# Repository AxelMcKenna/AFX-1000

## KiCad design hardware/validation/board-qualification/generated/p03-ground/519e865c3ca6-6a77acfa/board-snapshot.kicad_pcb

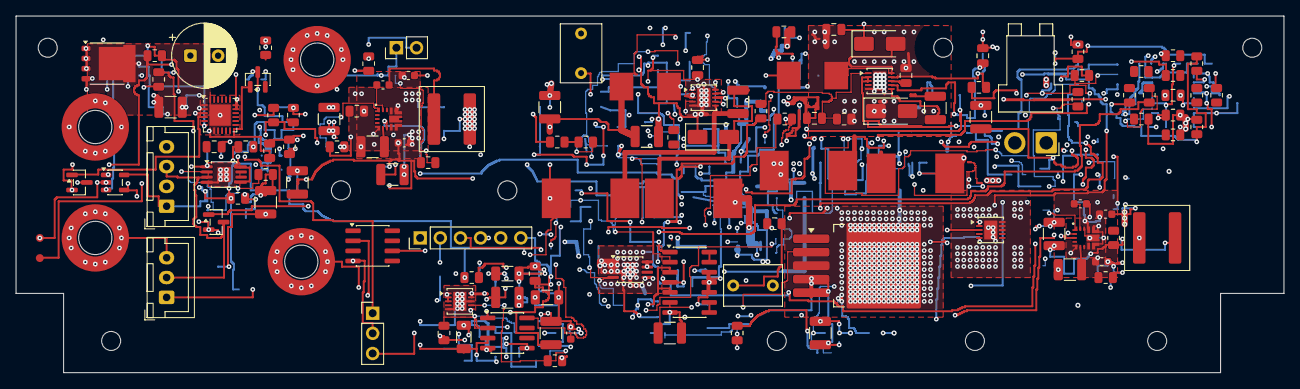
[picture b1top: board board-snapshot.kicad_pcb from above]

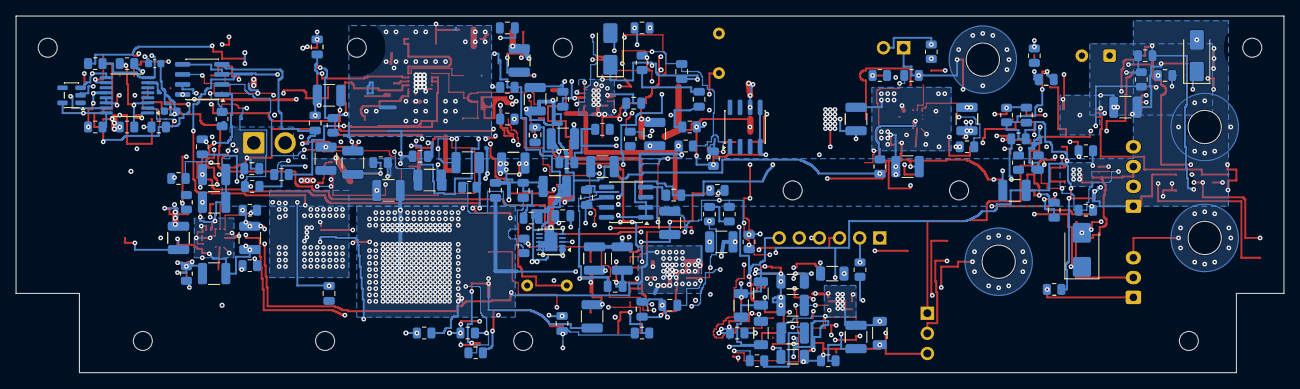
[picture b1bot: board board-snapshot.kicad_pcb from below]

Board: 6 copper layers, 160.0 x 45.0 mm, 261 parts (129 on the bottom side), 108 nets.

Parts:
C1, C63: 10uF 63V X7R; C_1210_3225Metric
C2, C3, C5, C6, C8, C9, C37, C42, C52, C57, C64, C65, C67, C68, C70: 22uF 50V X7R; C_1210_3225Metric
C4, C7, C10, C35, C38, C40, C43, C50, C53, C55, C58, C59, C61, C66, C69, C71: 100nF 50V X7R; C_0805_2012Metric
C11, C30, C72, C107, C108: 100nF 16V X7R; C_0805_2012Metric
C12, C14, C73, C75: 68pF 50V C0G 5%; C_0805_2012Metric
C13, C15, C74, C76: 330nF 16V X7R; C_0805_2012Metric
C31: 2.2uF 16V X7R; C_0805_2012Metric
C32, C33: 1uF film 63V 10% MKS2C041001F00KSSD; C_Rect_L7.2mm_W5.0mm_P5.00mm
C34, C39, C49, C54, C240: 47nF 50V C0G 5%; C_1210_3225Metric
C36, C41, C51, C56: 10uF 50V X7R; C_1210_3225Metric
C60, C62, C105: 1uF 50V X7R; C_0805_2012Metric
C101, C102: 2.2uF 100V X7R; C_1210_3225Metric
C103: 220uF 35V electrolytic 20% (EEUFR1V221); CP_Radial_D8.0mm_P3.50mm
C104: 1uF 50V X7R; C_1210_3225Metric
C106: 10uF 16V X7R; C_1210_3225Metric
C109: 1nF 16V C0G 5%; C_0805_2012Metric
C110: 10nF 16V C0G 5%; C_0805_2012Metric
C200, C220: 4.7uF 16V X7R; C_1210_3225Metric
C201, C202, C203, C221, C222, C223, C255, C301, C302: 100nF 50V X7R; C_0603_1608Metric
C204, C205, C224, C225: 22uF 25V X7R; C_1210_3225Metric
C206, C207, C208, C209, C226, C227, C228, C229: 47uF 16V X7R; C_1210_3225Metric
C241: 1uF 25V X7R; C_1210_3225Metric
C242, C243, C244, C245, C246, C247, C248, C249, C250, C251: 100nF 25V C0G 5% KEMET C1206C104J3GACTU; C_1206_3216Metric
C252, C253: 1uF 16V X7R; C_1210_3225Metric
C254: 22uF 16V X7R; C_1210_3225Metric
C300: 10nF 50V C0G 5%; C_0805_2012Metric
D1, D2, D3, D4, D103: SS16-E3/61T; D_SMA
D101: SMBJ33CA-E3/52; D_SMB
D102: BAS116,215; SOT-23
H1, H2, H3, H4, H5, H6, H7, H8, H9, H10: M2_CLEARANCE; M2_Clearance
J2: Header6; PinHeader_1x06_P2.54mm_Vertical
J3: Header2; PinHeader_1x02_P2.54mm_Vertical
J20, J21, J23, J24: Wurth 7466003R M3 SMT; Wurth_7466003R
J22: P03 READY test; PinHeader_1x03_P2.54mm_Vertical
J101: JST B2PS-VH (VHR-2N/SVH-41T-P1.1 AWG16); JST_VH_B2PS-VH_1x02_P3.96mm_Horizontal
J103: Bare POWER_READY probe pads, no fitted header; Probe2_P2.54_D1
J104: JST B3B-XH-A (XHP-3/SXH-001T-P0.6); JST_XH_B3B-XH-A_1x03_P2.50mm_Vertical
J106: JST B4B-XH-A (XHP-4/SXH-001T-P0.6); JST_XH_B4B-XH-A_1x04_P2.50mm_Vertical
L1, L6: 33uH 20% SRP7050WA-330M; SRP7050WA
L2, L3, L7, L8: 68uH 20% SRP1050WA-680M; SRP1050WA
L20, L23: 4.7uH 20% Coilcraft XAL7030-472MEC; L_Coilcraft_XAL7030-472
Q101: PSMN012-100YL,115; LFPAK56
Q102: BSS138-7-F; SOT-23
Q103: DMN2056U-7; SOT-23
R1: 300k 0.01% 5ppm; R_0805_2012Metric
R2, R3, R4, R45, R46: 15k 0.01% 5ppm; R_0805_2012Metric
R5, R20, R21, R34, R35: 330k 0.01% 5ppm; R_0805_2012Metric
R6, R7, R49, R50, R316: 4.7k 1%; R_0805_2012Metric
R17, R19, R110: 1k 1%; R_0805_2012Metric
R18, R120: 100k 1%; R_0805_2012Metric
R22, R27, R36, R41, R243, R244: 100k 0.01% 5ppm; R_0805_2012Metric
R23, R28, R37, R42, R241: 6.8k 1%; R_0805_2012Metric
R24, R38: 9.09k 1%; R_0805_2012Metric
R25, R39, R47, R306: 200k 0.01% 5ppm; R_0805_2012Metric
R26, R40, R308: 180k 0.01% 5ppm; R_0805_2012Metric
R29, R43: 5.62k 1%; R_0805_2012Metric
R44: 240k 0.01% 5ppm; R_0805_2012Metric
R48, R301, R303, R305, R307, R309, R314: 10k 0.01% 5ppm; R_0805_2012Metric
R101, R103, R117: 309k 0.1% 10ppm; R_0805_2012Metric
R102: 40.2k 0.1% 10ppm; R_0805_2012Metric
R104: 28k 0.1% 10ppm; R_0805_2012Metric
R105: 68.1k 0.1% 10ppm; R_0805_2012Metric
R106, R109, R118, R119: 10k 0.1% 10ppm; R_0805_2012Metric
R107: 4.02k 0.1% 10ppm; R_0805_2012Metric
R108: 11.4k 0.1% 10ppm; R_0805_2012Metric
R111, R204, R224, R246: 10k 1%; R_0805_2012Metric
R112, R114: 47k 1%; R_0805_2012Metric
R113: 3.3k 1%; R_0805_2012Metric
R115: 30.9k 0.1% 10ppm; R_0805_2012Metric
R116: 3.09k 0.1% 10ppm; R_0805_2012Metric
R121: 100 1%; R_0805_2012Metric
R130: 49.9 0.01% 5ppm; R_0805_2012Metric
R200: 9k 0.01% 2ppm Susumu RG2012L-902-L-T1; R_0805_2012Metric
R201: 1k 0.01% 2ppm Susumu RG2012L-102-L-T1; R_0805_2012Metric
R202, R222: 24.3k 1%; R_0805_2012Metric
R203, R223: 3.32k 1%; R_0805_2012Metric
R205, R225: 22k 1%; R_0805_2012Metric
R206: 54.9 0.1% 25ppm Panasonic ERA6AEB549V; R_0805_2012Metric
R220: 11k 0.01% 5ppm; R_0805_2012Metric
R221, R311: 1k 0.01% 5ppm; R_0805_2012Metric
R240: 100 0.01% 5ppm; R_0805_2012Metric
R242: 120 0.01% 5ppm; R_0805_2012Metric
R245: 2.21k 1%; R_0805_2012Metric
R300, R302: 87.6k 0.01% 5ppm; R_0805_2012Metric
R304: 324k 0.01% 5ppm; R_0805_2012Metric
R310: 590 0.01% 5ppm; R_0805_2012Metric
R312: 7.5k 0.01% 5ppm; R_0805_2012Metric
R313: 1M 0.01% 5ppm; R_0805_2012Metric
R315: 750k 0.01% 5ppm; R_0805_2012Metric
U1, U13: LT3471EDD#PBF; DFN-10-1EP_3x3mm_P0.5mm_EP1.65x2.38mm
U4: REF5025EIDR; SOIC-8_3.9x4.9mm_P1.27mm
U5: OPA4192ID; SOIC-14_3.9x8.7mm_P1.27mm
U6, U24: OPA2192ID; SOIC-8_3.9x4.9mm_P1.27mm
U7: LT3080IMS8E#PBF; MSOP-8-1EP_3x3mm_P0.65mm_EP1.68x1.88mm
U8: LT3080IQ#PBF; TO-263-5_TabPin3
U10, U11: LT3090IDD#PBF; DFN-10-1EP_3x3mm_P0.5mm_EP1.65x2.38mm
U12: LT1634AIS8-2.5#PBF; SOIC-8_3.9x4.9mm_P1.27mm
U20, U23: TPS543620RPYR; TPS543620_RPY0014A
U21: ADR4550BRZ; SOIC-8_3.9x4.9mm_P1.27mm
U22: LT3045IDD#PBF; DFN-10-1EP_3x3mm_P0.5mm_EP1.65x2.38mm
U25: LTC2910HGN#PBF; SSOP-16_3.9x4.9mm_P0.635mm
U26: SN74LVC1G08DBVR; SOT-23-5
U101: TPS26630RGER; Texas_RGE0024H_VQFN-24-1EP_4x4mm_P0.5mm_EP2.7x2.7mm
U102: TPS7A1601DGNR; MSOP-8-1EP_3x3mm_P0.65mm_EP1.68x1.88mm
U103: TLV7011DBVR; SOT-23-5

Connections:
/5V_DIG_SRC: C30.1, C206.1, C207.1, C208.1, C209.1, J3.1, J23.1, L20.2, R6.1, R7.1, R49.1, R50.1, R200.1, R300.1, U4.1, U4.2, U10.5, U11.5
/AGND: C2.2, C3.2, C4.2, C5.2, C6.2, C7.2, C8.2, C9.2, C10.2, C11.2, C13.2, C15.2, C30.2, C31.2, C32.2, C33.2, C35.2, C36.2, C37.2, C38.2, C40.2, C41.2, C42.2, C43.2, C50.2, C51.2, C52.2, C53.2, C55.2, C56.2, C57.2, C58.2, C59.2, C60.2, C61.2, C62.2, C64.2, C65.2, C66.2, C67.2, C68.2, C69.2, C70.2, C71.2, C72.2, C74.2, C76.2, C101.2, C102.2, C103.2, C104.2, C105.2, C106.2, C107.2, C108.2, C109.2, C110.2, C200.2, C202.2, C203.2, C204.2, C205.2, C206.2, C207.2, C208.2, C209.2, C220.2, C222.2, C223.2, C224.2, C225.2, C226.2, C227.2, C228.2, C229.2, C241.2, C242.2, C243.2, C244.2, C245.2, C246.2, C247.2, C248.2, C249.2, C250.2, C251.2, C252.2, C253.2, C254.2, C255.2, C300.2, C301.2, C302.2, D2.1, D4.1, D101.2, D103.2, J2.2, J3.2, J20.1, J21.1, J22.2, J101.2, J103.1, J104.3, J106.2, Q103.2, R3.2, R22.2, R24.2, R27.2, R29.2, R36.2, R38.2, R41.2, R43.2, R45.2, R102.2, R104.2, R106.2, R107.2, R109.2, R111.2, R112.2, R114.2, R116.2, R119.2, R120.2, R201.2, R202.2, R203.2, R205.2, R221.2, R222.2, R223.2, R225.2, R243.2, R245.2, R301.2, R303.2, R305.2, R307.2, R309.2, R311.2, U1.5, U1.11, U4.4, U5.10, U5.11, U5.12, U6.8, U10.3, U11.3, U12.6, U13.5, U13.11, U20.5, U20.9, U20.11, U21.4, U22.5, U22.8, U22.11, U23.5, U23.9, U23.11, U24.4, U24.5, U25.9, U25.13, U25.14, U26.3, U101.8, U101.25, U102.4, U102.9, U103.2
/AUX_FB: R109.1, R130.2, U102.2
/AUX_START_DELAY: C110.1, U102.7
/BLOCK_DRV: Q102.1, U101.4
/BLOCK_GATE: Q101.4, Q102.3, U101.3
/CUK_NODE: C1.2, D2.2, L3.1
/DC_IN: C101.1, D101.1, J101.1, Q101.1, Q101.2, Q101.3, Q102.2, R101.1, R103.1, U101.5
/FAST_OV_GATE: Q103.1, R120.1, R121.2
/FAST_OV_OUT: R117.1, R121.1, U103.1
/FAST_OV_REF: C109.1, R118.2, R119.1, U103.4
/FAST_OV_SENSE: R115.2, R116.1, R117.2, U103.3
/INPUT_ILIM: R107.1, U101.10
/INPUT_OV: D102.1, R103.2, R104.1, U101.7
/INPUT_PGTH: R105.2, R106.1, U101.15
/INPUT_SLEW: C105.1, U101.9
/INPUT_UV: R101.2, R102.1, U101.6
/LO_CUK_NODE: C63.2, D4.2, L8.1
/LO_N_FB: C75.2, R46.2, R47.1, U13.4
/LO_N_RMID: R47.2, R48.1
/LO_N_SS: C76.1, R50.2, U13.7
/LO_N_SW: C63.1, L7.2, U13.6
/LO_P_FB: C73.2, R44.2, R45.1, U13.1
/LO_P_SS: C74.1, R49.2, U13.9
/LO_P_SW: D3.2, L6.2, U13.10
/LO_REF_1V: C72.1, R46.1, U13.2, U13.3
/N12_DRIVE: C54.1, R42.1, U6.7
/N12_FB: C54.2, R40.2, R41.1, U6.6
/N12_RMID: R39.2, R40.1
/N12_SET: C55.1, R39.1, R42.2, U11.4
/N12_SRC: C57.1, C58.1, J2.5, R43.1, R315.2, U11.1, U11.2
/N19_DRIVE: C49.1, R37.1, U6.1
/N19_FB: C49.2, R35.2, R36.1, U6.2
/N19_RMID: R34.2, R35.1
/N19_SET: C50.1, R34.1, R37.2, U10.4
/N19_SRC: C52.1, C53.1, J2.3, R38.1, R313.2, U10.1, U10.2
/NREF_2V5: R18.1, R19.1, U12.4, U12.5
/NREF_FILTER: C33.1, R19.2, U6.3, U6.5
/P03_ALL_SOURCES_READY: J22.1, J106.4, R316.2, U25.12
/P03_ANA_DIV: R242.2, R243.1, R244.1
/P03_ANA_DRIVE: C240.1, R241.1, U24.1
/P03_ANA_FB: C240.2, R244.2, U24.2
/P03_ANA_SET: C241.1, R241.2, R242.1, U22.7
/P03_AUX_TRIM: R108.2, R130.1
/P03_A_BOOT: C221.1, U23.14
/P03_A_BP5: C220.1, U23.6
/P03_A_ENABLE: R224.2, R225.1, U23.7
/P03_A_FB: R220.2, R221.1, U23.4
/P03_A_FSEL: R222.1, U23.1
/P03_A_MODE: R223.1, U23.2
/P03_A_SW: C221.2, L23.1, U23.10, U23.13
/P03_D_BOOT: C201.1, U20.14
/P03_D_BP5: C200.1, U20.6
/P03_D_ENABLE: R204.2, R205.1, U20.7
/P03_D_FB: R201.1, R206.2, U20.4
/P03_D_FB_TRIM: R200.2, R206.1
/P03_D_FSEL: R202.1, U20.1
/P03_D_MODE: R203.1, U20.2
/P03_D_SW: C201.2, L20.1, U20.10, U20.13
/P03_MON_ANA: R302.2, R303.1, U25.2
/P03_MON_BUCK_OK: U25.5, U26.4
/P03_MON_DIG: R300.2, R301.1, U25.1
/P03_MON_N12: R314.2, R315.1, U25.8
/P03_MON_N19: R312.2, R313.1, U25.7
/P03_MON_NEG_BIAS: R310.2, R311.1, R312.1, R314.1
/P03_MON_P12: R306.2, R307.1, U25.4
/P03_MON_P19: R304.2, R305.1, U25.3
/P03_MON_REF: R310.1, U25.10
/P03_MON_TIMER: C300.1, U25.15
/P03_MON_VIN: R308.2, R309.1, U25.6
/P03_PRE6V: C226.1, C227.1, C228.1, C229.1, C253.1, L23.2, R220.1, U21.2, U22.1, U22.2, U22.3, U22.6
/P03_REF5: C252.1, R240.1, U21.6
/P03_REF_FILTER: C242.1, C243.1, C244.1, C245.1, C246.1, C247.1, C248.1, C249.1, C250.1, C251.1, R240.2, U24.3
/P03_SOURCES_READY: R246.2, U20.3, U23.3, U26.1
/P03_SPARE_24: U24.6, U24.7
/P03_SPARE_C: U5.8, U5.9
/P12_DRIVE: C39.1, R28.1, U5.7
/P12_FB: C39.2, R26.2, R27.1, U5.6
/P12_RMID: R25.2, R26.1
/P12_SET: C40.1, R25.1, R28.2, U8.2
/P12_SRC: C42.1, C43.1, J2.4, R29.1, R306.1, U8.3
/P19_DRIVE: C34.1, R23.1, U5.1
/P19_FB: C34.2, R21.2, R22.1, U5.2
/P19_RMID: R20.2, R21.1
/P19_SET: C35.1, R20.1, R23.2, U7.4
/P19_SRC: C37.1, C38.1, J2.1, R24.1, R304.1, U7.1, U7.2, U7.3, U7.9
/POWER_READY: J22.3, J103.2, R110.2, R204.1, R224.1, U26.2, U101.16
/POWER_RUN: J104.2, J106.3, Q103.3, R112.1, U101.12, U102.3
/PREF_2V5: C31.1, R17.1, U4.6
/PREF_FILTER: C32.1, R17.2, U5.3, U5.5
/RAW_N17: C56.1, C67.1, C68.1, C69.1, C75.1, L8.2, R48.2, U11.8, U11.9, U11.10, U11.11
/RAW_N22: C8.1, C9.1, C10.1, C14.1, C51.1, C61.1, C62.1, L3.2, R5.2, R18.2, U6.4, U10.8, U10.9, U10.10, U10.11
/RAW_N_FB: C14.2, R4.2, R5.1, U1.4
/RAW_N_SS: C15.1, R7.2, U1.7
/RAW_N_SW: C1.1, L2.2, U1.6
/RAW_P17: C41.1, C64.1, C65.1, C66.1, C73.1, D3.1, R44.1, U8.4, U8.5
/RAW_P22: C5.1, C6.1, C7.1, C12.1, C36.1, C59.1, C60.1, D1.1, R1.1, U5.4, U7.5, U7.7, U7.8
/RAW_P_FB: C12.2, R2.2, R3.1, U1.1
/RAW_P_RMID: R1.2, R2.1
/RAW_P_SS: C13.1, R6.2, U1.9
/RAW_P_SW: D1.2, L1.2, U1.10
/SPARE_OUT: U5.13, U5.14
/SWITCH_SUPPLY: J104.1, R113.2
/SW_REF_1V: C11.1, R4.1, U1.2, U1.3
/V2V5_AUX: C106.1, C107.1, C108.1, C301.1, C302.1, D102.3, J106.1, R108.1, R110.1, R111.1, R113.1, R118.1, R246.1, R316.1, U25.16, U26.5, U102.1, U103.5
/V5_REG_SRC: C254.1, J2.6, J24.1, R245.1, R302.1, U22.9, U22.10
/VIN_IC: C102.1, Q101.5, R115.1, U101.1, U101.2, U102.5, U102.8
/VIN_PROTECTED: C2.1, C3.1, C4.1, C70.1, C71.1, C103.1, C104.1, C202.1, C203.1, C204.1, C205.1, C222.1, C223.1, C224.1, C225.1, C255.1, D103.1, L1.1, L2.1, L6.1, L7.1, R105.1, R114.1, R308.1, U1.8, U13.8, U20.8, U20.12, U23.8, U23.12, U24.8, U101.17, U101.18

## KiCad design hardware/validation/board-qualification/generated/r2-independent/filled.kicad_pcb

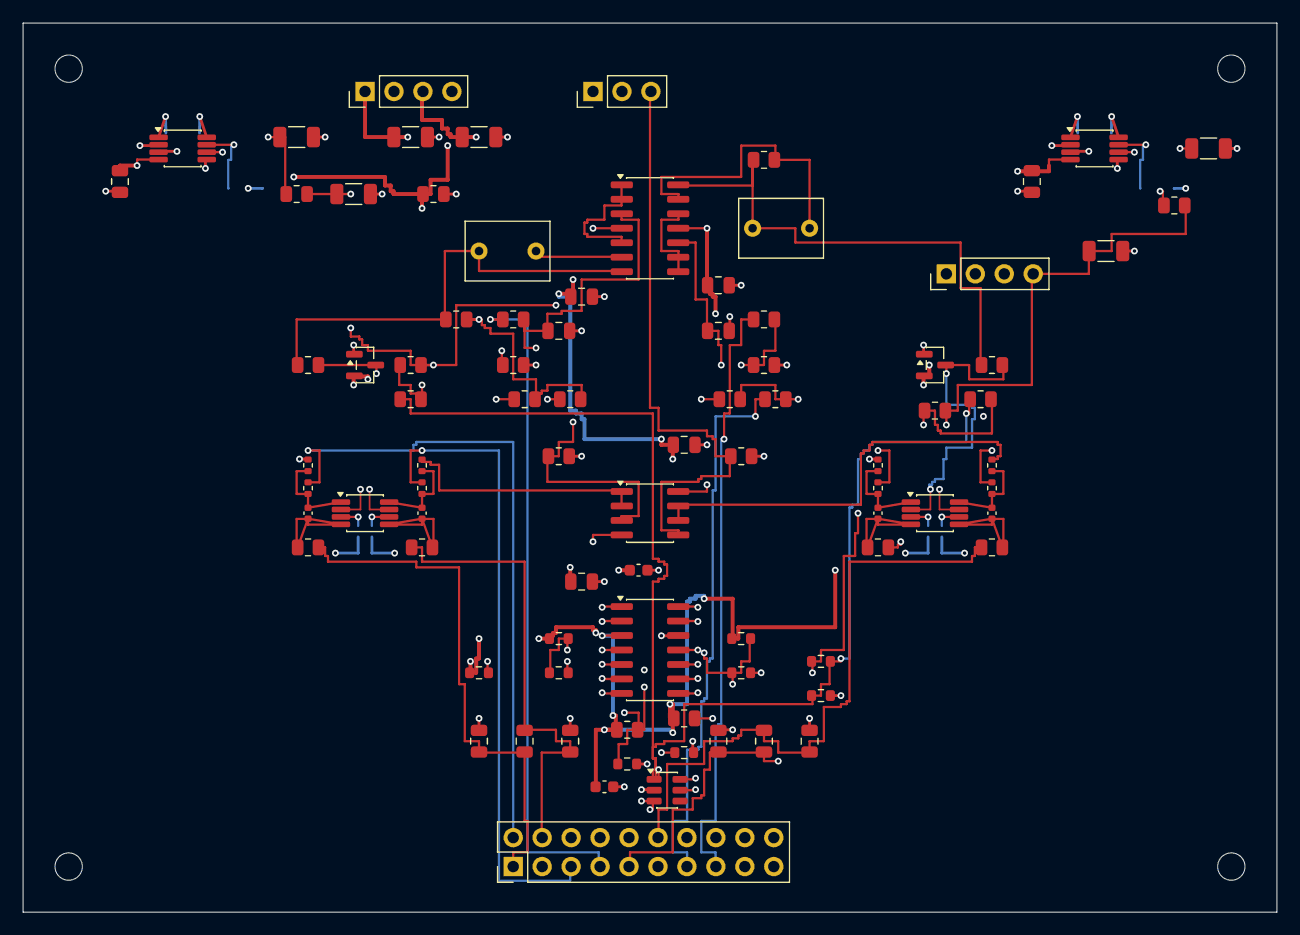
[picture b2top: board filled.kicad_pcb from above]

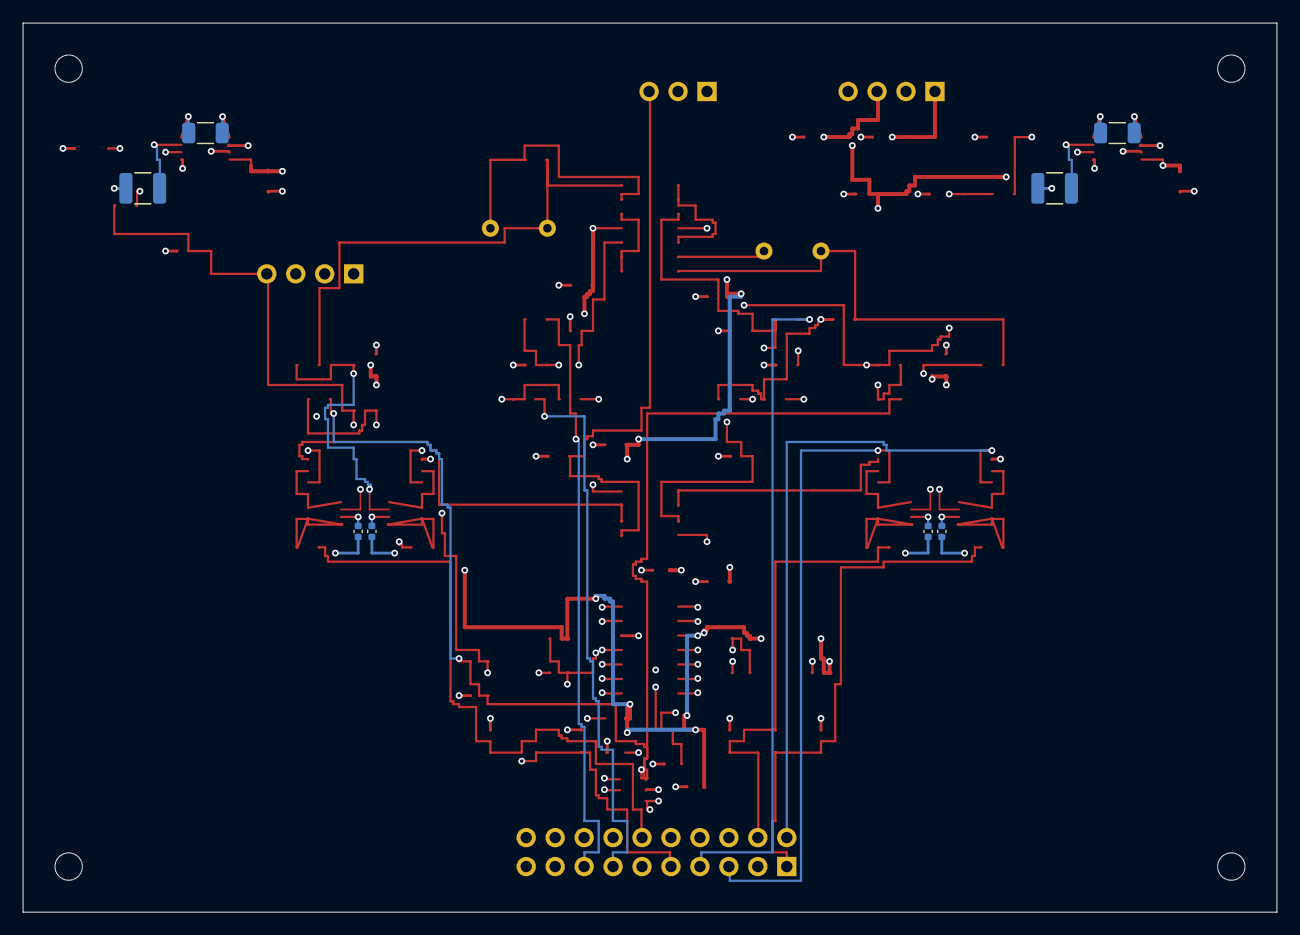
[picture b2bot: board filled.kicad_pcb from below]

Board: 6 copper layers, 110.0 x 78.0 mm, 98 parts (8 on the bottom side), 55 nets.

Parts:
C1, C2, C15, C16: 1pF C0G +/-0.1pF; C_0402_1005Metric
C3, C17: 47pF C0G 5%; C_0805_2012Metric
C4, C5, C18, C19: 22pF C0G 5%; C_0805_2012Metric
C6, C20: 100nF 25V X7R; C_0805_2012Metric
C7, C21: 1uF 63V film 10%; C_Rect_L7.2mm_W5.0mm_P5.00mm
C8, C22: 10uF 16V X7R; C_1206_3216Metric
C9, C23: 47uF 25V X7S; C_1210_3225Metric
C10, C11, C24, C25: 47uF 6.3V X7S; C_1206_3216Metric
C12, C26: 2.2uF 16V X7R; C_0805_2012Metric
C13, C14, C27, C28: 100nF 16V X7R; C_0402_1005Metric
C29, C30, C31, C32: 100nF 50V X7R; C_0805_2012Metric
C33, C34: 10uF 50V X7R; C_1206_3216Metric
C35, C36: 100nF 16V X7R; C_0603_1608Metric
D1, D2: BAT54S,215; SOT-23
H1, H2, H3, H4: M2_CLEARANCE; M2_Clearance
J1: Conn_01x03; PinHeader_1x03_P2.54mm_Vertical
J2: Conn_02x10_Odd_Even; PinHeader_2x10_P2.54mm_Vertical
J3, J4: Conn_01x04; PinHeader_1x04_P2.54mm_Vertical
R1, R2, R17, R18: 2.49k 0.05%; R_0402_1005Metric
R3, R4, R19, R20: 1.21k 0.05%; R_0402_1005Metric
R5, R6, R21, R22: 3.3R 1%; R_0805_2012Metric
R7, R23: 1M 1%; R_0805_2012Metric
R8, R9, R24, R25: 100k 0.01%; R_0805_2012Metric
R10, R11, R26, R27: 10k 0.1%; R_0805_2012Metric
R12, R28: 10M 1%; R_0805_2012Metric
R13, R29: 10k 1%; R_0805_2012Metric
R14, R30: 47k 1%; R_0805_2012Metric
R15, R31: 68k 1%; R_0805_2012Metric
R16, R32: 0.1R 1%; R_0805_2012Metric
R33: 1k 1%; R_0805_2012Metric
R34, R36: 100k 0.01%; R_0603_1608Metric
R35, R37, R39, R41: 10k 0.01%; R_0603_1608Metric
R38: 161k 0.01%; R_0805_2012Metric
R40: 240k 0.01%; R_0805_2012Metric
R42, R43: 10k 1%; R_0603_1608Metric
R44: 100k 1%; R_0603_1608Metric
U1, U2: THS4551IDGKR; VSSOP-8_3x3mm_P0.65mm
U3: OPA1656ID; SOIC-8_3.9x4.9mm_P1.27mm
U4: OPA4192ID; SOIC-14_3.9x8.7mm_P1.27mm
U5, U6: LM7705MM/NOPB; VSSOP-8_3x3mm_P0.65mm
U7: TLV9024DR; SOIC-14_3.9x8.7mm_P1.27mm
U8: TPS3808G50DBVR; SOT-23-6

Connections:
/ADC_LN: C3.2, C5.1, J2.4, R6.2
/ADC_LP: C3.1, C4.1, J2.1, R5.2
/ADC_RN: C17.2, C19.1, J2.12, R22.2
/ADC_RP: C17.1, C18.1, J2.9, R21.2
/AGND: C4.2, C5.2, C6.2, C9.2, C10.2, C11.2, C12.2, C13.2, C14.2, C18.2, C19.2, C20.2, C23.2, C24.2, C25.2, C26.2, C27.2, C28.2, C29.2, C30.2, C31.2, C32.2, C33.2, C34.2, C35.2, C36.2, D1.1, D2.1, J1.2, J2.3, J2.6, J2.8, J2.11, J2.14, J2.16, J2.20, J3.2, J4.1, R2.1, R7.2, R9.2, R18.1, R23.2, R25.2, R33.2, R39.2, R41.2, R44.2, U5.2, U5.3, U5.5, U6.2, U6.3, U6.5, U7.12, U8.2
/BIAS_OK: J2.18, R42.2, U7.1, U7.2, U7.13, U7.14, U8.3
/BIAS_SHIFT_L: R34.2, R35.1, U7.4, U7.7
/BIAS_SHIFT_R: R36.2, R37.1, U7.8, U7.11
/BUF_L: R1.1, U3.1, U3.2
/BUF_R: R17.1, U3.6, U3.7
/CM_DRIVE_L: C7.1, R12.1, R13.1, U4.7
/CM_DRIVE_R: C21.1, R28.1, R29.1, U4.14
/CM_SENSE_L: C7.2, R10.2, R11.2, R12.2, U4.6
/CM_SENSE_R: C21.2, R26.2, R27.2, R28.2, U4.13
/DRV_ENABLE: J2.19, J4.2, R43.1
/DRV_LN: C1.1, R6.1, U1.5
/DRV_LP: C2.1, R5.1, U1.4
/DRV_RN: C15.1, R22.1, U2.5
/DRV_RP: C16.1, R21.1, U2.4
/FB_N_L: C2.2, R2.2, R4.2, U1.1
/FB_N_R: C16.2, R18.2, R20.2, U2.1
/FB_P_L: C1.2, R1.2, R3.2, U1.8
/FB_P_R: C15.2, R17.2, R19.2, U2.8
/FLY_N_L: C8.2, U5.8
/FLY_N_R: C22.2, U6.8
/FLY_P_L: C8.1, U5.1
/FLY_P_R: C22.1, U6.1
/N12: C30.1, C32.1, C34.1, J3.3, U3.4, U4.11
/NBIAS_L: C11.1, C14.1, J4.3, R15.2, R16.2, R35.2, U1.6
/NBIAS_R: C25.1, C28.1, J4.4, R31.2, R32.2, R37.2, U2.6
/NPUMP_L: C10.1, R16.1, U5.6
/NPUMP_R: C24.1, R32.1, U6.6
/P12: C29.1, C31.1, C33.1, J3.1, U3.8, U4.4
/PD_GATED: J2.17, R14.1, R30.1, R43.2, R44.1, U8.1
/PD_L: R14.2, R15.1, U1.7
/PD_R: R30.2, R31.1, U2.7
/PRE_OUT_L: J1.1, R7.1, U3.3
/PRE_OUT_R: J1.3, R23.1, U3.5
/REF_ADC1: J2.7, R8.1
/REF_ADC2: J2.15, R24.1
/REF_DIV_L: C6.1, R8.2, R9.1, U4.3
/REF_DIV_R: C20.1, R24.2, R25.1, U4.10
/REF_HALF_L: U4.1, U4.2, U4.5
/REF_HALF_R: U4.8, U4.9, U4.12
/RES_L: C9.1, U5.7
/RES_R: C23.1, U6.7
/SENSE_LN: J2.5, R3.1, R11.1
/SENSE_LP: J2.2, R4.1, R10.1
/SENSE_RN: J2.13, R19.1, R27.1
/SENSE_RP: J2.10, R20.1, R26.1
/THRESH_LOWER: R40.2, R41.1, U7.6, U7.10
/THRESH_UPPER: R38.2, R39.1, U7.5, U7.9
/V5_REG: C12.1, C13.1, C26.1, C27.1, C35.1, C36.1, D1.2, D2.2, J3.4, R33.1, R34.1, R36.1, R38.1, R40.1, R42.1, U1.3, U2.3, U5.4, U6.4, U7.3, U8.5, U8.6
/VOCM_L: D1.3, R13.2, U1.2
/VOCM_R: D2.3, R29.2, U2.2
